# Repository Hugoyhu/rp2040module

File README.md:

# rp2040module
RP2040 Module. Based off Raspberry PI Foundation's schematics.

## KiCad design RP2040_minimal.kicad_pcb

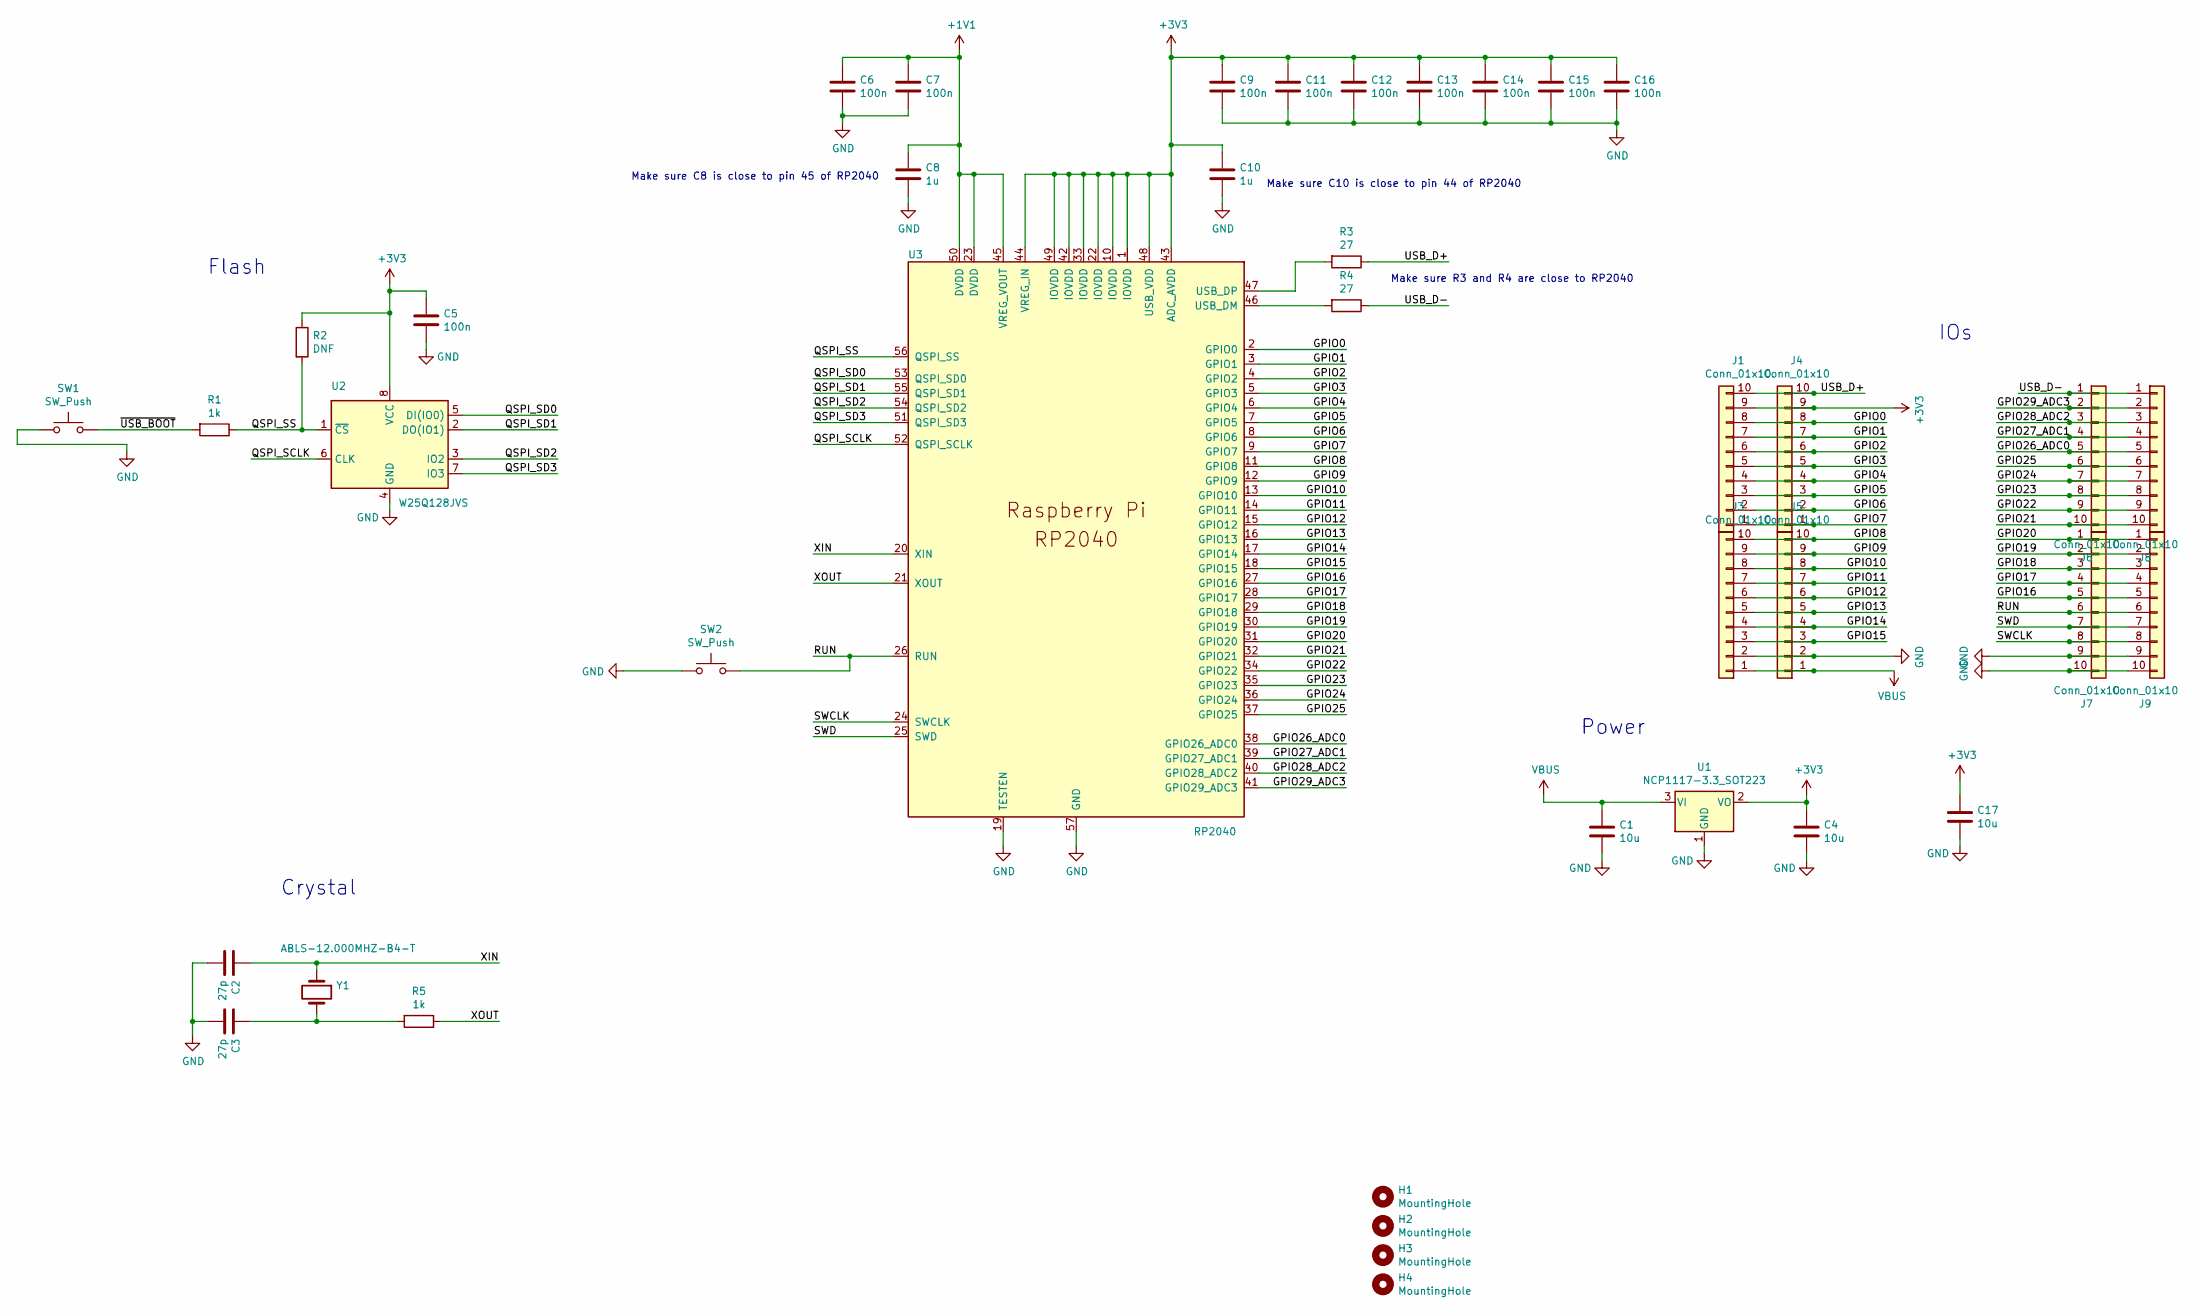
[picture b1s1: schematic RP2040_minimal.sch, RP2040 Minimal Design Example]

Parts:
C1, C4, C17: 10u; C_0805_2012Metric
C2, C3: 27p; C_0402_1005Metric
C5, C6, C7, C9, C11, C12, C13, C14, C15, C16: 100n; C_0402_1005Metric
C8, C10: 1u; C_0402_1005Metric
H1, H2, H3, H4: MountingHole; MountingHole_2.7mm_M2.5
J1, J3, J4, J5, J6, J7, J8, J9: Conn_01x10; PinSocket_1x10_P2.54mm_Vertical
R1, R5: 1k; C_0402_1005Metric
R2: DNF; C_0402_1005Metric
R3, R4: 27; C_0402_1005Metric
SW1, SW2: SW_Push; SW_SPST_B3U-1000P
U1: NCP1117-3.3_SOT223; SOT-223-3_TabPin2
U2: W25Q128JVS; SOIC-8_5.23x5.23mm_P1.27mm
U3: RP2040; RP2040-QFN-56
Y1: ABLS-12.000MHZ-B4-T; Crystal_SMD_5032-2Pin_5.0x3.2mm

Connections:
+1V1: C6.1, C7.1, C8.1, U3.23 (DVDD), U3.45 (VREG_VOUT), U3.50 (DVDD)
+3V3: C4.1, C5.1, C9.1, C10.1, C11.1, C12.1, C13.1, C14.1, C15.1, C16.1, C17.1, J1.9, J4.9, R2.1, U1.2 (VO), U2.8 (VCC), U3.1 (IOVDD), U3.10 (IOVDD), U3.22 (IOVDD), U3.33 (IOVDD), U3.42 (IOVDD), U3.43 (ADC_AVDD), U3.44 (VREG_IN), U3.48 (USB_VDD), U3.49 (IOVDD)
/GPIO0: J1.8, J4.8, U3.2 (GPIO0)
/GPIO1: J1.7, J4.7, U3.3 (GPIO1)
/GPIO2: J1.6, J4.6, U3.4 (GPIO2)
/GPIO3: J1.5, J4.5, U3.5 (GPIO3)
/GPIO4: J1.4, J4.4, U3.6 (GPIO4)
/GPIO5: J1.3, J4.3, U3.7 (GPIO5)
/GPIO6: J1.2, J4.2, U3.8 (GPIO6)
/GPIO7: J1.1, J4.1, U3.9 (GPIO7)
/GPIO8: J3.10, J5.10, U3.11 (GPIO8)
/GPIO9: J3.9, J5.9, U3.12 (GPIO9)
/GPIO10: J3.8, J5.8, U3.13 (GPIO10)
/GPIO11: J3.7, J5.7, U3.14 (GPIO11)
/GPIO12: J3.6, J5.6, U3.15 (GPIO12)
/GPIO13: J3.5, J5.5, U3.16 (GPIO13)
/GPIO14: J3.4, J5.4, U3.17 (GPIO14)
/GPIO15: J3.3, J5.3, U3.18 (GPIO15)
/GPIO16: J7.5, J9.5, U3.27 (GPIO16)
/GPIO17: J7.4, J9.4, U3.28 (GPIO17)
/GPIO18: J7.3, J9.3, U3.29 (GPIO18)
/GPIO19: J7.2, J9.2, U3.30 (GPIO19)
/GPIO20: J7.1, J9.1, U3.31 (GPIO20)
/GPIO21: J6.10, J8.10, U3.32 (GPIO21)
/GPIO22: J6.9, J8.9, U3.34 (GPIO22)
/GPIO23: J6.8, J8.8, U3.35 (GPIO23)
/GPIO24: J6.7, J8.7, U3.36 (GPIO24)
/GPIO25: J6.6, J8.6, U3.37 (GPIO25)
/GPIO26_ADC0: J6.5, J8.5, U3.38 (GPIO26_ADC0)
/GPIO27_ADC1: J6.4, J8.4, U3.39 (GPIO27_ADC1)
/GPIO28_ADC2: J6.3, J8.3, U3.40 (GPIO28_ADC2)
/GPIO29_ADC3: J6.2, J8.2, U3.41 (GPIO29_ADC3)
/QSPI_SCLK: U2.6 (CLK), U3.52 (QSPI_SCLK)
/QSPI_SD0: U2.5 (DI(IO0)), U3.53 (QSPI_SD0)
/QSPI_SD1: U2.2 (DO(IO1)), U3.55 (QSPI_SD1)
/QSPI_SD2: U2.3 (IO2), U3.54 (QSPI_SD2)
/QSPI_SD3: U2.7 (IO3), U3.51 (QSPI_SD3)
/QSPI_SS: R1.1, R2.2, U2.1 (~CS), U3.56 (QSPI_SS)
/RUN: J7.6, J9.6, SW2.2, U3.26 (RUN)
/SWCLK: J7.8, J9.8, U3.24 (SWCLK)
/SWD: J7.7, J9.7, U3.25 (SWD)
/USB_D+: J1.10, J4.10, R3.1
/USB_D-: J6.1, J8.1, R4.1
/XIN: C2.1, U3.20 (XIN), Y1.1
/XOUT: R5.1, U3.21 (XOUT)
/~USB_BOOT: R1.2, SW1.2
GND: C1.2, C2.2, C3.2, C4.2, C5.2, C6.2, C7.2, C8.2, C9.2, C10.2, C11.2, C12.2, C13.2, C14.2, C15.2, C16.2, C17.2, J3.2, J5.2, J7.9, J7.10, J9.9, J9.10, SW1.1, SW2.1, U1.1 (GND), U2.4 (GND), U3.19 (TESTEN), U3.57 (GND)
unnamed: C3.1, R5.2, Y1.2
unnamed: R3.2, U3.47 (USB_DP)
unnamed: R4.2, U3.46 (USB_DM)
VBUS: C1.1, J3.1, J5.1, U1.3 (VI)

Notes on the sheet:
Make sure C10 is close to pin 44 of RP2040
Make sure C8 is close to pin 45 of RP2040
Crystal
Flash
Power
IOs
Make sure R3 and R4 are close to RP2040

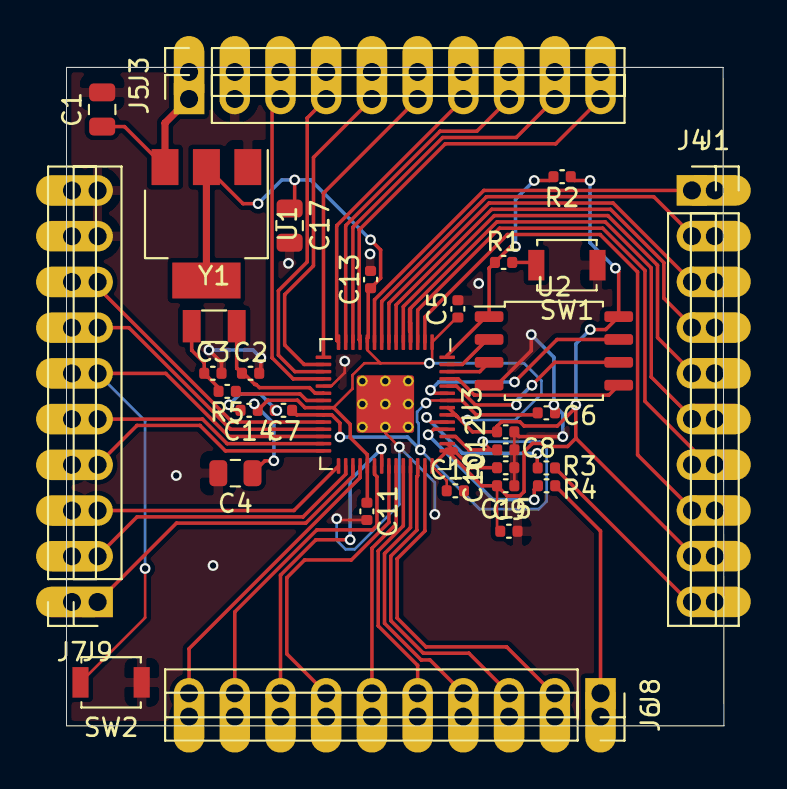
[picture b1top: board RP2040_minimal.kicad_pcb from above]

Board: 2 copper layers, 36.5 x 36.6 mm, 36 parts (0 on the bottom side), 51 nets.
